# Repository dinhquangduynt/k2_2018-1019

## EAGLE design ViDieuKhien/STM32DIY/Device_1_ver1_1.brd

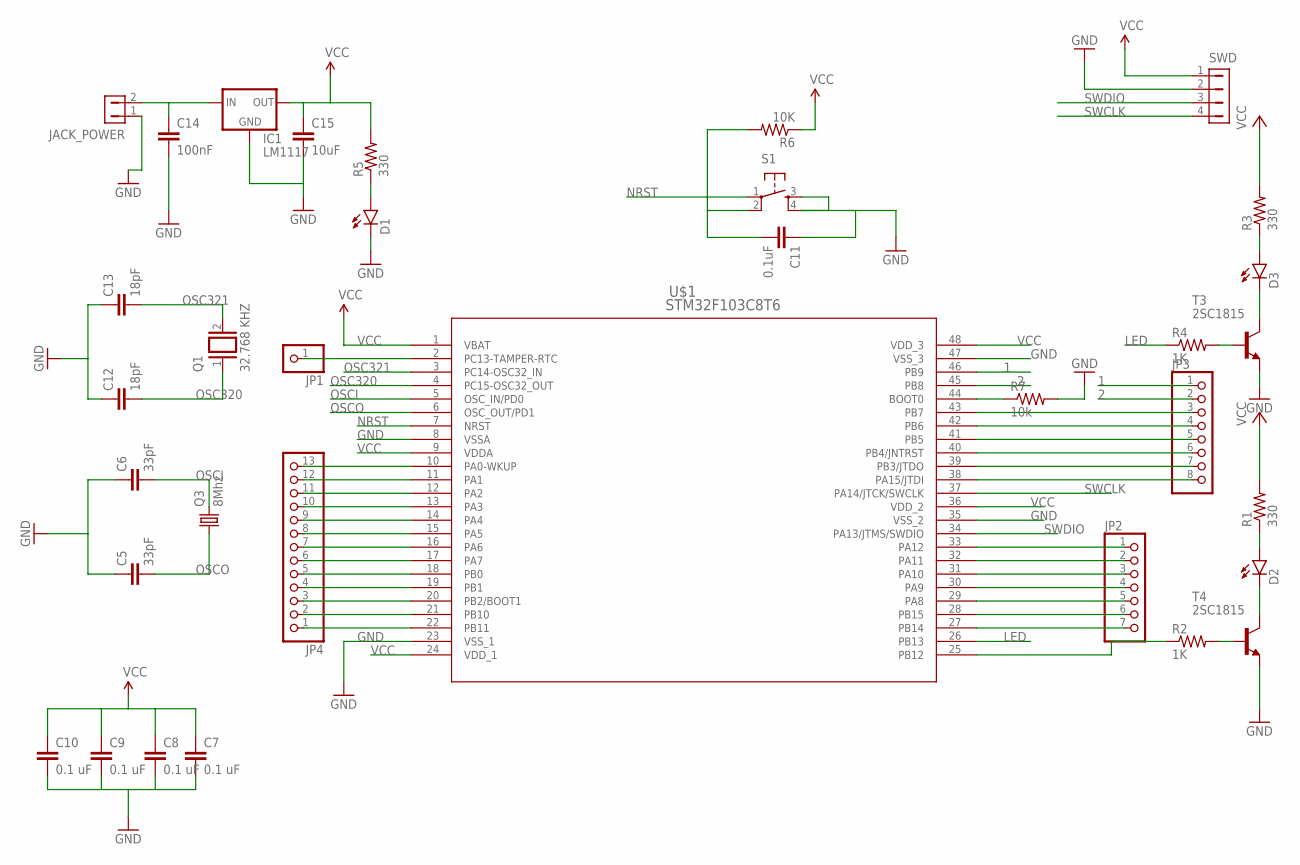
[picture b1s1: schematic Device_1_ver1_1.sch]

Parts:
C5, C6: 33pF; CAP-PTH-SMALL
C7, C8, C9, C10: 0.1 uF; CAP-PTH-SMALL
C11: 0.1uF; CAP-PTH-SMALL
C12, C13: 18pF; CAP-PTH-SMALL
C14: 100nF; CAP-PTH-SMALL
C15: 10uF; CAP-PTH-SMALL
D1, D2, D3: LED5MM
IC1: LM1117; SOT223
JACK_POWER: HDR-1X2-MTE-100; MTE-100-2V
JP1: PINHD-1X1; 1X01
JP2: PINHD-1X7; 1X07
JP3: PINHD-1X8; 1X08
JP4: PINHD-1X13; 1X13
Q1: 32.768 KHZ; QS
Q3: 8Mhz; HC49/S
R1, R3, R5: 330; AXIAL-0.4
R2, R4: 1K; AXIAL-0.4
R6: 10K; AXIAL-0.4
R7: 10k; AXIAL-0.4
S1: TAC_SWITCHPTH; TACTILE-PTH
SWD: HDR-1X4-MTE-100; MTE-100-4V
T3, T4: 2SC1815; TO92-ECB
U$1: STM32F103C8T6; LQFP48

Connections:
1: JP3.1, U$1.46 (PB9)
2: JP3.2, U$1.45 (PB8)
GND: C5.1, C6.1, C7.2, C8.2, C9.2, C10.2, C11.1, C12.1, C13.1, C14.2, C15.2, D1.K (C), IC1.1 (GND), JACK_POWER.1, R7.P$2 (2), S1.3, S1.4, SWD.2, T3.E, T4.E, U$1.8 (VSSA), U$1.23 (VSS_1), U$1.35 (VSS_2), U$1.47 (VSS_3)
LED: R4.P$1 (1), U$1.26 (PB13)
unnamed: D2.A, R1.P$1 (1)
unnamed: C14.1, IC1.3 (IN), JACK_POWER.2
unnamed: JP1.1, U$1.2 (PC13-TAMPER-RTC)
unnamed: R7.P$1 (1), U$1.44 (BOOT0)
unnamed: JP3.8, U$1.38 (PA15/JTDI)
unnamed: JP3.7, U$1.39 (PB3/JTDO)
unnamed: JP3.6, U$1.40 (PB4/JNTRST)
unnamed: R4.P$2 (2), T3.B
unnamed: JP3.5, U$1.41 (PB5)
unnamed: JP3.4, U$1.42 (PB6)
unnamed: JP3.3, U$1.43 (PB7)
unnamed: D2.K (C), T4.C
unnamed: R2.P$2 (2), T4.B
unnamed: D3.K (C), T3.C
unnamed: D3.A, R3.P$1 (1)
unnamed: D1.A, R5.P$1 (1)
unnamed: R2.P$1 (1), U$1.25 (PB12)
unnamed: JP4.13, U$1.10 (PA0-WKUP)
unnamed: JP4.12, U$1.11 (PA1)
unnamed: JP4.11, U$1.12 (PA2)
unnamed: JP4.10, U$1.13 (PA3)
unnamed: JP4.9, U$1.14 (PA4)
unnamed: JP4.8, U$1.15 (PA5)
unnamed: JP4.7, U$1.16 (PA6)
unnamed: JP4.6, U$1.17 (PA7)
unnamed: JP4.5, U$1.18 (PB0)
unnamed: JP4.4, U$1.19 (PB1)
unnamed: JP4.3, U$1.20 (PB2/BOOT1)
unnamed: JP4.2, U$1.21 (PB10)
unnamed: JP4.1, U$1.22 (PB11)
unnamed: JP2.1, U$1.33 (PA12)
unnamed: JP2.2, U$1.32 (PA11)
unnamed: JP2.3, U$1.31 (PA10)
unnamed: JP2.4, U$1.30 (PA9)
unnamed: JP2.5, U$1.29 (PA8)
unnamed: JP2.6, U$1.28 (PB15)
unnamed: JP2.7, U$1.27 (PB14)
NRST: C11.2, R6.P$2 (2), S1.1, S1.2, U$1.7 (NRST)
OSC320: C12.2, Q1.1, U$1.4 (PC15-OSC32_OUT)
OSC321: C13.2, Q1.2, U$1.3 (PC14-OSC32_IN)
OSCI: C6.2, Q3.2, U$1.5 (OSC_IN/PD0)
OSCO: C5.2, Q3.1, U$1.6 (OSC_OUT/PD1)
SWCLK: SWD.4, U$1.37 (PA14/JTCK/SWCLK)
SWDIO: SWD.3, U$1.34 (PA13/JTMS/SWDIO)
VCC: C7.1, C8.1, C9.1, C10.1, C15.1, IC1.2 (OUT), R1.P$2 (2), R3.P$2 (2), R5.P$2 (2), R6.P$1 (1), SWD.1, U$1.1 (VBAT), U$1.9 (VDDA), U$1.24 (VDD_1), U$1.36 (VDD_2), U$1.48 (VDD_3)

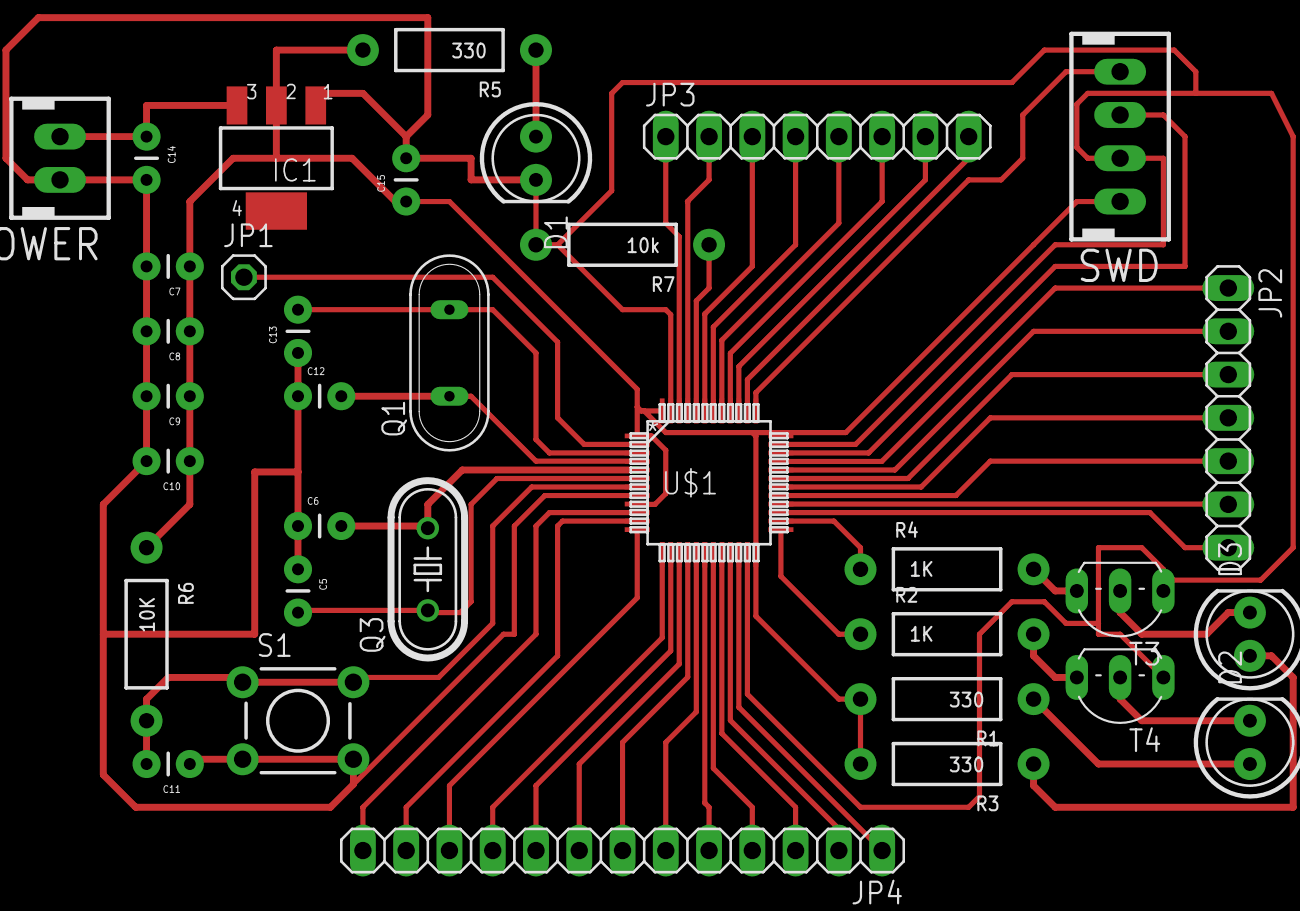
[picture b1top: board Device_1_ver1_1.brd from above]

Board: 2 copper layers, 34 parts (0 on the bottom side), 49 nets.

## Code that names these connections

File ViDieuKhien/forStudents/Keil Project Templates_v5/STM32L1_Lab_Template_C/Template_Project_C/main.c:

//******************** (C) Yifeng ZHU ********************
// @file    main.c
// @author  Yifeng Zhu
// @version V1.0.0
// @date    November-11-2012
// @note    
// @brief   C code for STM32L1xx Discovery Kit
// @note
//          This code is for the book "Embedded Systems with ARM Cortex-M3 
//          Microcontrollers in Assembly Language and C, Yifeng Zhu, 
//          ISBN-10: 0982692625.
// @attension
//          This code is provided for education purpose. The author shall not be 
//          held liable for any direct, indirect or consequential damages, for any 
//          reason whatever. More information can be found from book website: 
//          http://www.eece.maine.edu/~zhu/book
//********************************************************

#include <stdint.h>

/* Standard STM32L1xxx driver headers */
#include "stm32l1xx.h"

/* STM32L1xx Discovery Kit:
    - USER Pushbutton: connected to PA0 (GPIO Port A, PIN 0), CLK RCC_AHBENR_GPIOAEN
    - RESET Pushbutton: connected RESET
    - GREEN LED: connected to PB7 (GPIO Port B, PIN 7), CLK RCC_AHBENR_GPIOBEN 
    - BLUE LED: connected to PB6 (GPIO Port B, PIN 6), CLK RCC_AHBENR_GPIOBEN
    - Linear touch sensor/touchkeys: PA6, PA7 (group 2),  PC4, PC5 (group 9),  PB0, PB1 (group 3)
*/



//******************************************************************************************
//* The main program starts here
//******************************************************************************************

int main(void){

	// Enable High Speed Internal Clock (HSI)
  RCC->CR |= ((uint32_t)RCC_CR_HSION);
	
	// wait until HSI is ready
	while ( (RCC->CR & (uint32_t) RCC_CR_HSIRDY) == 0 ) {;}
	
	// Select HSI as system clock source 
  RCC->CFGR &= (uint32_t)((uint32_t)~(RCC_CFGR_SW));
  RCC->CFGR |= (uint32_t)RCC_CFGR_SW_HSI;

  // Wait till HSI is used as system clock source 
  while ((RCC->CFGR & (uint32_t)RCC_CFGR_SWS) == 0 ) {;}
  
	// Enable the clock to GPIO Port B	
	RCC->AHBENR		|= 0x00000002;   

	GPIOB->MODER  &= ~(0x03<<(2*6)) ;   // Clear bit 13 and bit 12

	// Dead loop & program hangs here
	while(1);
}

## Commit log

2020-10-03 push source

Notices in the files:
parts and their libraries:
SparkFun-Capacitors: Licensing: Creative Commons ShareAlike 4.0 International - https://creativecommons.org/licenses/by-sa/4.0
con-hdrs40: Copyright (C) 2004, Bob Starr (bobstarr@mindspring.com)
stm32lib: Copyright (C) 2015 Accelerated Designs. All rights reserved
